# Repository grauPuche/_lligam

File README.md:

# v02

The point of this version is to take the already working device and make it wireless. To do so I'm using the well known ESP8266. this is going to take the analog data from the joystick and send it to a node server. This is the main objective of this version.

The plan for the following is to have a client side for the mentioned information. And to do the first steps towards the creation of the final iteration of the controller and make the custom board I need for it.

---

## HARDWARE

**As of april 8th**, the webSocket enabled joystick is completely functional, *.ino* is sending data properly and server is displaying it at [lligam.grrau.co](http://lligam.grrrau.co). There are still some things to be adjusted and others to be added, but the core functionality is working exactly as intended. At this point the next step is building the multiplexer to have both axis of the joystick read by one pin.

---

**As of march 8th**, *.ino* code working, X & Y values are not showing properly. either a hardware.wiring problem, or a code/pinout issue. the issue is that I was dumb enough to switch the meaning of analog with PWD. and feather only has one analogRead Pin. Wiring has to be UPDATED.

---

## what I'm using

As mentioned; a [HUZZAH feather](https://www.adafruit.com/product/2821)  with ESP8266 from Adafruit. to run the basic operations needed before designing the PCB. Where I'll be using [this](https://www.adafruit.com/product/2491).

To set everything up, I've been following the [tutorials given by Adafruit](https://learn.adafruit.com/adafruit-feather-huzzah-esp8266)

---

## SOFTWARE

**As of march 8th** the third version of the software is up and running. This v. is the first step to completion. At this point there are two servers running through *grrrau.co*, one is a **webSocket** server (called *mitjons*) and the other on is a simple **express** server (called *lligam*). *Mitjons* is getting the data from the *esp8266* and sending it to *lligam* which interprets and displays it. The next step in software is to instead of displaying this information is using it to read the patterns and use it to link it to the required movements from the joystick.

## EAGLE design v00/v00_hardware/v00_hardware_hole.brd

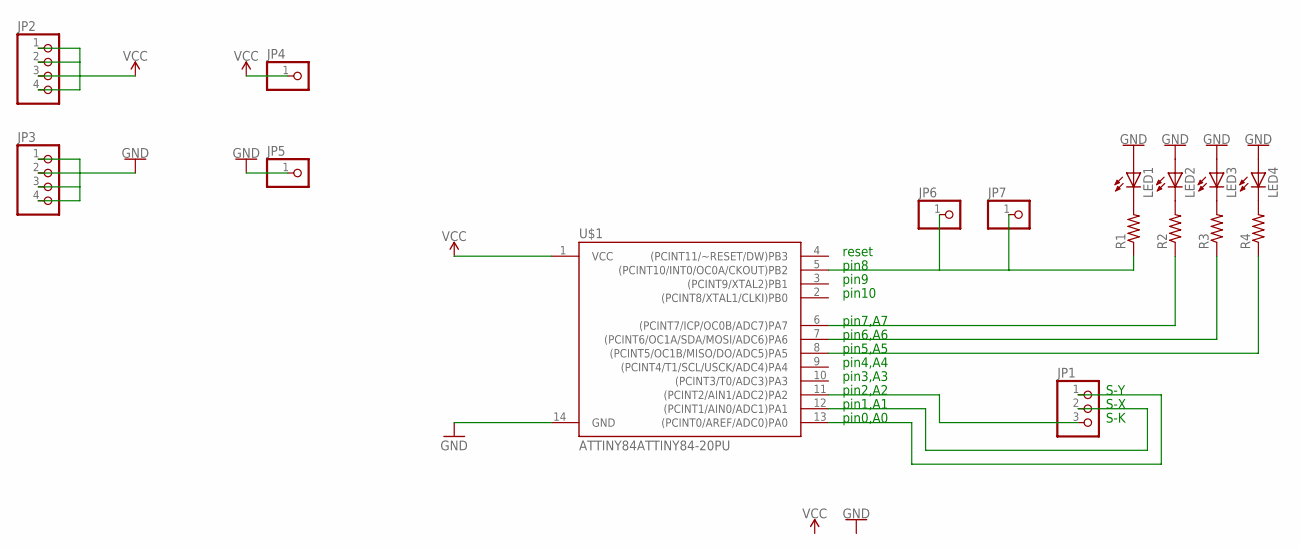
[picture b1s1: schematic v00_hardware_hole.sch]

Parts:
JP1: PINHD-1X3; 1X03
JP2, JP3: PINHD-1X4; 1X04
JP4, JP5, JP6, JP7: PINHD-1X1; 1X01
LED1, LED2, LED3, LED4: LED5MM
R1, R2, R3, R4: R-US_0204/7; 0204/7
U$1: ATTINY84ATTINY84-20PU; DIP14

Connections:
GND: JP3.1, JP3.2, JP3.3, JP3.4, JP5.1, LED1.A, LED2.A, LED3.A, LED4.A, U$1.14 (GND)
unnamed: LED1.K (C), R1.2
unnamed: LED2.K (C), R2.2
unnamed: LED3.K (C), R3.2
unnamed: LED4.K (C), R4.2
unnamed: JP1.1, U$1.13 ((PCINT0/AREF/ADC0)PA0)
unnamed: JP1.2, U$1.12 ((PCINT1/AIN0/ADC1)PA1)
unnamed: JP6.1, JP7.1, R1.1, U$1.5 ((PCINT10/INT0/OC0A/CKOUT)PB2)
unnamed: R2.1, U$1.6 ((PCINT7/ICP/OC0B/ADC7)PA7)
unnamed: R3.1, U$1.7 ((PCINT6/OC1A/SDA/MOSI/ADC6)PA6)
unnamed: R4.1, U$1.8 ((PCINT5/OC1B/MISO/DO/ADC5)PA5)
unnamed: JP1.3, U$1.11 ((PCINT2/AIN1/ADC2)PA2)
VCC: JP2.1, JP2.2, JP2.3, JP2.4, JP4.1, U$1.1 (VCC)

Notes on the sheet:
S-Y
S-X
S-K
pin10
pin9
pin8
pin7,A7
pin6,A6
pin5,A5
pin4,A4
pin3,A3
pin2,A2
pin1,A1
pin0,A0
reset

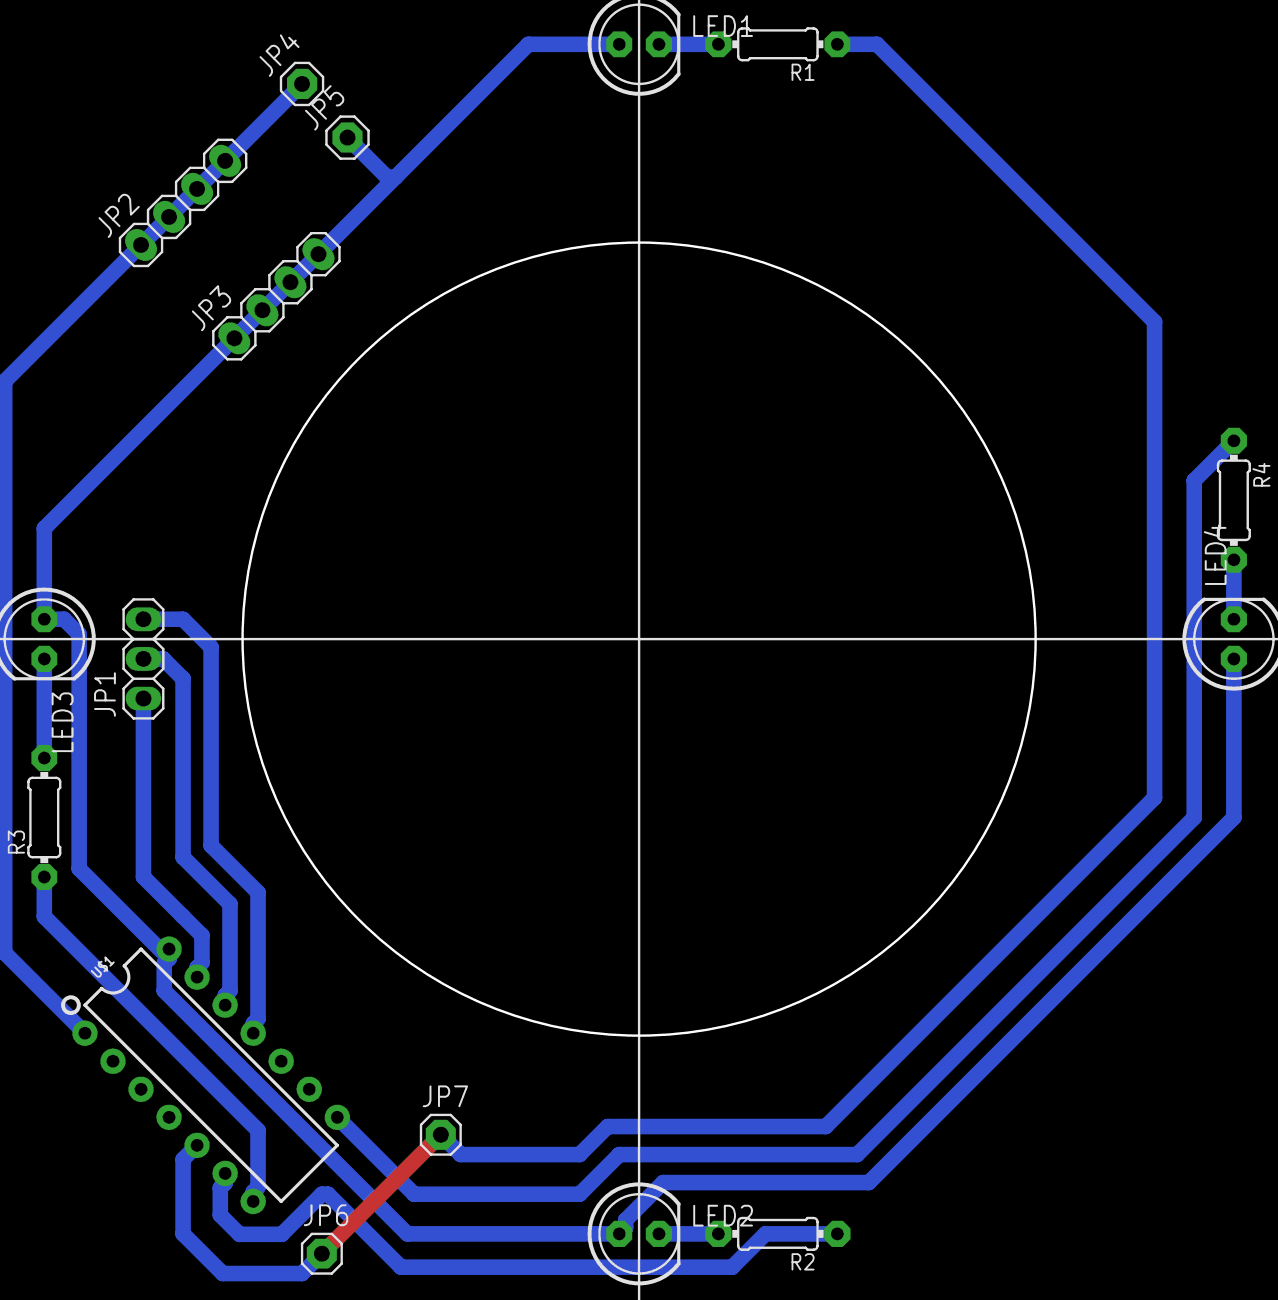
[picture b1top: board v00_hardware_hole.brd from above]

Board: 2 copper layers, 16 parts (0 on the bottom side), 13 nets.

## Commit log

2018-03-07 hardware changes
2018-03-09 v02 dir + mac address .ino file
2018-03-09 readme added + eagle Files for the feather
2018-03-09 Updates in v02 hardware
2018-03-09 readme update w issues
2018-03-09 update issues in README
2018-03-09 update issues readme
2018-03-26 v02 software + updated general hardware
2018-04-06 [v02] hardware - v02 complete
2018-04-09 [v03] update - readme and v03 is live
2018-04-09 [lligam] add - photos
2018-04-09 [lligam] fix - image size

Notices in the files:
parts and their libraries:
SparkFun-IC-Microcontroller: Licensing: Creative Commons ShareAlike 4.0 International - https://creativecommons.org/licenses/by-sa/4.0
